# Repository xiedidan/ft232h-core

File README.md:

# ft232h-core
# Target
I created this project to:  
  1. collect documents and reference designs for FT232H;  
  2. proof of FT232H in sync mode.  
  
# Reason  
I found some open source FT232H sync mode IPs (from opencore, blogs, etc.. you could find these in ip-core dir in this project), but they all seem to lose 1 byte data every 512 bytes on my BeMicro CV + UM232H system.  
After some researching I found that the real timing for FT232H is different from the timing in its datasheet.  
So here's this little project to figure out the real timing for FT232H.  

# Status  
3 sub-projects are completed:  
  1. ft232h-speed-test - VC++ project for PC side, receiving speed counter and error detector;  
  2. ft232h_simple - super simple POC (proof of concept) verilog project for FT232H sync mode;  
  3. ft232h_fifo - coupled FT232H write logic (device to PC) to Altera on-chip DCFIFO IP.  
  
38MByte/sec device to PC transfer speed is archived on my Win10 PC.  
There are always 2 bytes of error at the beginning of transfer, but after that no error is observed.  
Now that's enough for me.

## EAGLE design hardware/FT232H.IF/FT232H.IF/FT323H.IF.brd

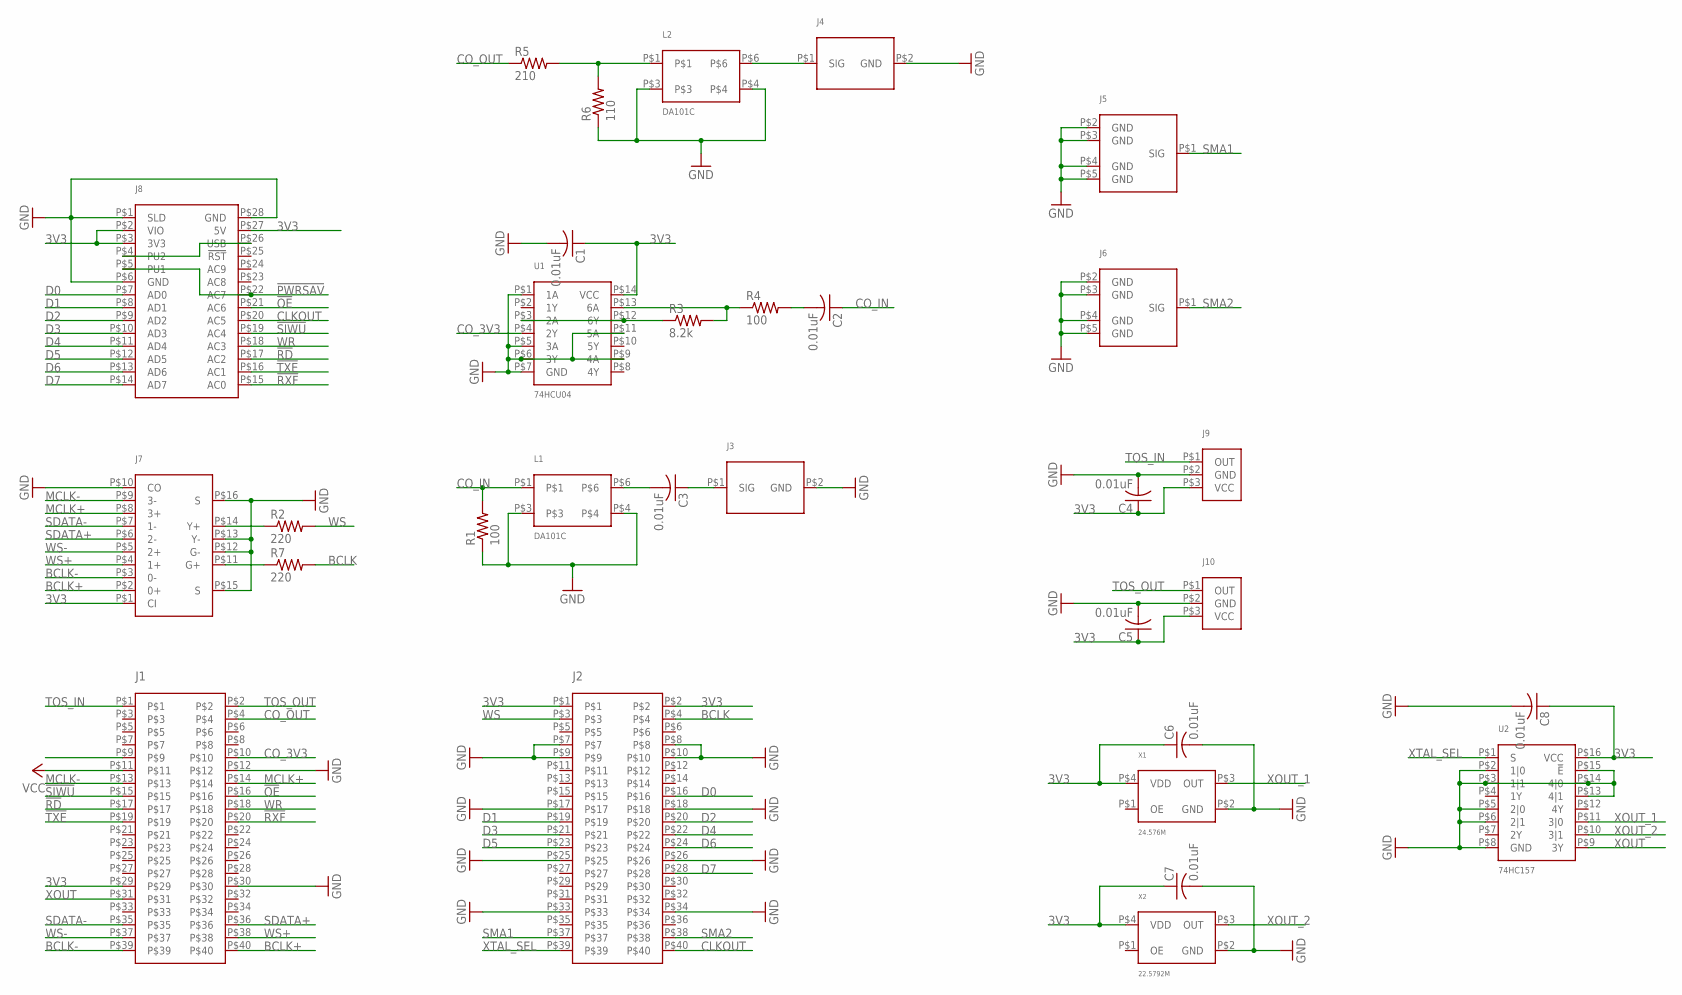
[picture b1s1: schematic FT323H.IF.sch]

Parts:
C1, C4, C5, C6, C7, C8: 0.01uF; C0805
C2, C3: 0.01uF; MKS2
J1, J2: JUMPER-2X20; JUMPER-2X20-2.54MM
J3, J4: RCA
J5, J6: SMA
J7: HR911130C
J8: UM232H
J9, J10: TORX178A
L1, L2: DA101C
R1, R4: 100; RJ-24
R2, R7: 220; RJ-24
R3: 8.2k; RJ-24
R5: 210; RJ-24
R6: 110; RJ-24
U1: 74HCU04; 74HCU04D
U2: 74HC157; 74HC157D-SO16
X1: 24.576M; SIT8208-0507
X2: 22.5792M; SIT8208-0507

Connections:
3V3: C1.1, C4.1, C5.1, C6.1, C7.1, C8.1, J1.P$29, J2.P$1, J2.P$2, J7.P$1 (CI), J8.P$2 (VIO), J8.P$3 (3V3), J8.P$27 (5V), J9.P$3 (VCC), J10.P$3 (VCC), U1.P$14 (VCC), U2.P$16 (VCC), X1.P$4 (VDD), X2.P$4 (VDD)
!OE: J1.P$16, J8.P$21 (AC6)
!PWRSAV: J8.P$5 (PU1), J8.P$22 (AC7)
!RD: J1.P$17, J8.P$17 (AC2)
!RXF: J1.P$20, J8.P$15 (AC0)
!SIWU: J1.P$15, J8.P$19 (AC4)
!TXE: J1.P$19, J8.P$16 (AC1)
BCLK: J2.P$4, R7.P$2 (2)
BCLK+: J1.P$40, J7.P$2 (0+)
BCLK-: J1.P$39, J7.P$3 (0-)
CLKOUT: J2.P$40, J8.P$20 (AC5)
CO_3V3: J1.P$10, U1.P$4 (2Y)
CO_IN: C2.P$1 (1), L1.P$1, R1.P$2 (2)
CO_OUT: J1.P$4, R5.P$1 (1)
D0: J2.P$16, J8.P$7 (AD0)
D1: J2.P$19, J8.P$8 (AD1)
D2: J2.P$20, J8.P$9 (AD2)
D3: J2.P$21, J8.P$10 (AD3)
D4: J2.P$22, J8.P$11 (AD4)
D5: J2.P$23, J8.P$12 (AD5)
D6: J2.P$24, J8.P$13 (AD6)
D7: J2.P$28, J8.P$14 (AD7)
GND: C1.2, C4.2, C5.2, C6.2, C7.2, C8.2, J1.P$12, J1.P$30, J2.P$7, J2.P$8, J2.P$9, J2.P$10, J2.P$17, J2.P$18, J2.P$25, J2.P$26, J2.P$33, J2.P$34, J3.P$2 (GND), J4.P$2 (GND), J5.P$2 (GND), J5.P$3 (GND), J5.P$4 (GND), J5.P$5 (GND), J6.P$2 (GND), J6.P$3 (GND), J6.P$4 (GND), J6.P$5 (GND), J7.P$10 (CO), J7.P$12 (G-), J7.P$13 (Y-), J7.P$15 (S), J7.P$16 (S), J8.P$1 (SLD), J8.P$6 (GND), J8.P$28 (GND), J9.P$2 (GND), J10.P$2 (GND), L1.P$3, L1.P$4, L2.P$3, L2.P$4, R1.P$1 (1), R6.P$1 (1), U1.P$1 (1A), U1.P$5 (3A), U1.P$6 (3Y), U1.P$7 (GND), U1.P$9 (4A), U1.P$11 (5A), U2.P$2 (1|0), U2.P$3 (1|1), U2.P$5 (2|0), U2.P$6 (2|1), U2.P$8 (GND), U2.P$13 (4|1), U2.P$14 (4|0), U2.P$15 (!E), X1.P$2 (GND), X2.P$2 (GND)
MCLK+: J1.P$14, J7.P$8 (3+)
MCLK-: J1.P$13, J7.P$9 (3-)
unnamed: J4.P$1 (SIG), L2.P$6
unnamed: C3.P$2 (2), L1.P$6
unnamed: R3.P$2 (2), R4.P$1 (1), U1.P$13 (6A)
unnamed: C2.P$2 (2), R4.P$2 (2)
unnamed: C3.P$1 (1), J3.P$1 (SIG)
unnamed: R3.P$1 (1), U1.P$3 (2A), U1.P$12 (6Y)
unnamed: J8.P$4 (PU2), J8.P$26 (USB)
unnamed: L2.P$1, R5.P$2 (2), R6.P$2 (2)
unnamed: J7.P$14 (Y+), R2.P$1 (1)
unnamed: J7.P$11 (G+), R7.P$1 (1)
SDATA+: J1.P$36, J7.P$6 (2-)
SDATA-: J1.P$35, J7.P$7 (1-)
SMA1: J2.P$37, J5.P$1 (SIG)
SMA2: J2.P$38, J6.P$1 (SIG)
TOS_IN: J1.P$1, J9.P$1 (OUT)
TOS_OUT: J1.P$2, J10.P$1 (OUT)
VCC: J1.P$11
WR: J1.P$18, J8.P$18 (AC3)
WS: J2.P$3, R2.P$2 (2)
WS+: J1.P$38, J7.P$4 (1+)
WS-: J1.P$37, J7.P$5 (2+)
XOUT: J1.P$31, U2.P$9 (3Y)
XOUT_1: U2.P$11 (3|0), X1.P$3 (OUT)
XOUT_2: U2.P$10 (3|1), X2.P$3 (OUT)
XTAL_SEL: J2.P$39, U2.P$1 (S)

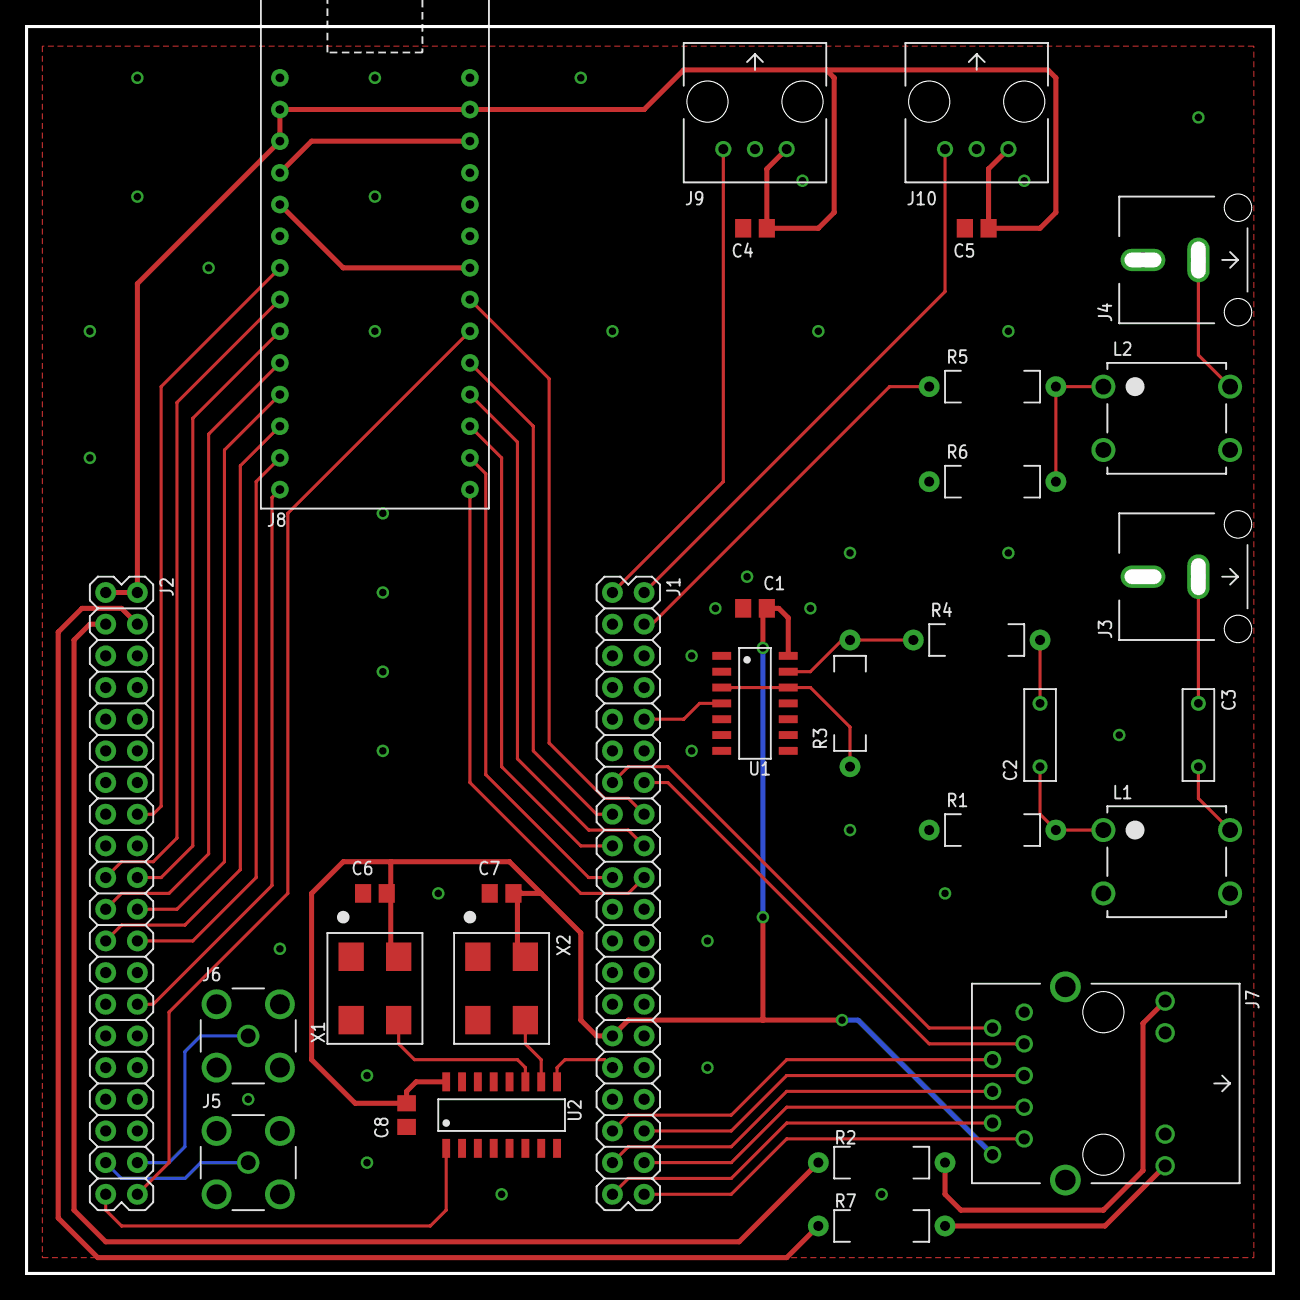
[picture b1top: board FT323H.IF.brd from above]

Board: 2 copper layers, 99.1 x 99.1 mm, 31 parts (0 on the bottom side), 49 nets.

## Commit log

2016-11-24 ft232h-speed-test program, modified for debug info
2016-11-24 collected docs, usb ip core. hardware interface design for bemicro cv
2016-11-25 super simple poc (proof of concept) verilog project for ft232h
2016-11-27 ft232h core with build-in fifo - only tx (dev -> pc) is implemented
2016-11-28 fixed errors when write_rdempty asserts
2016-12-05 clear all avalon enhancement from ft232h_fifo project, create ft232h_avalon for avalon version of ft232h core
2016-12-05 create ft232h_avalon project for avalon specific tests
